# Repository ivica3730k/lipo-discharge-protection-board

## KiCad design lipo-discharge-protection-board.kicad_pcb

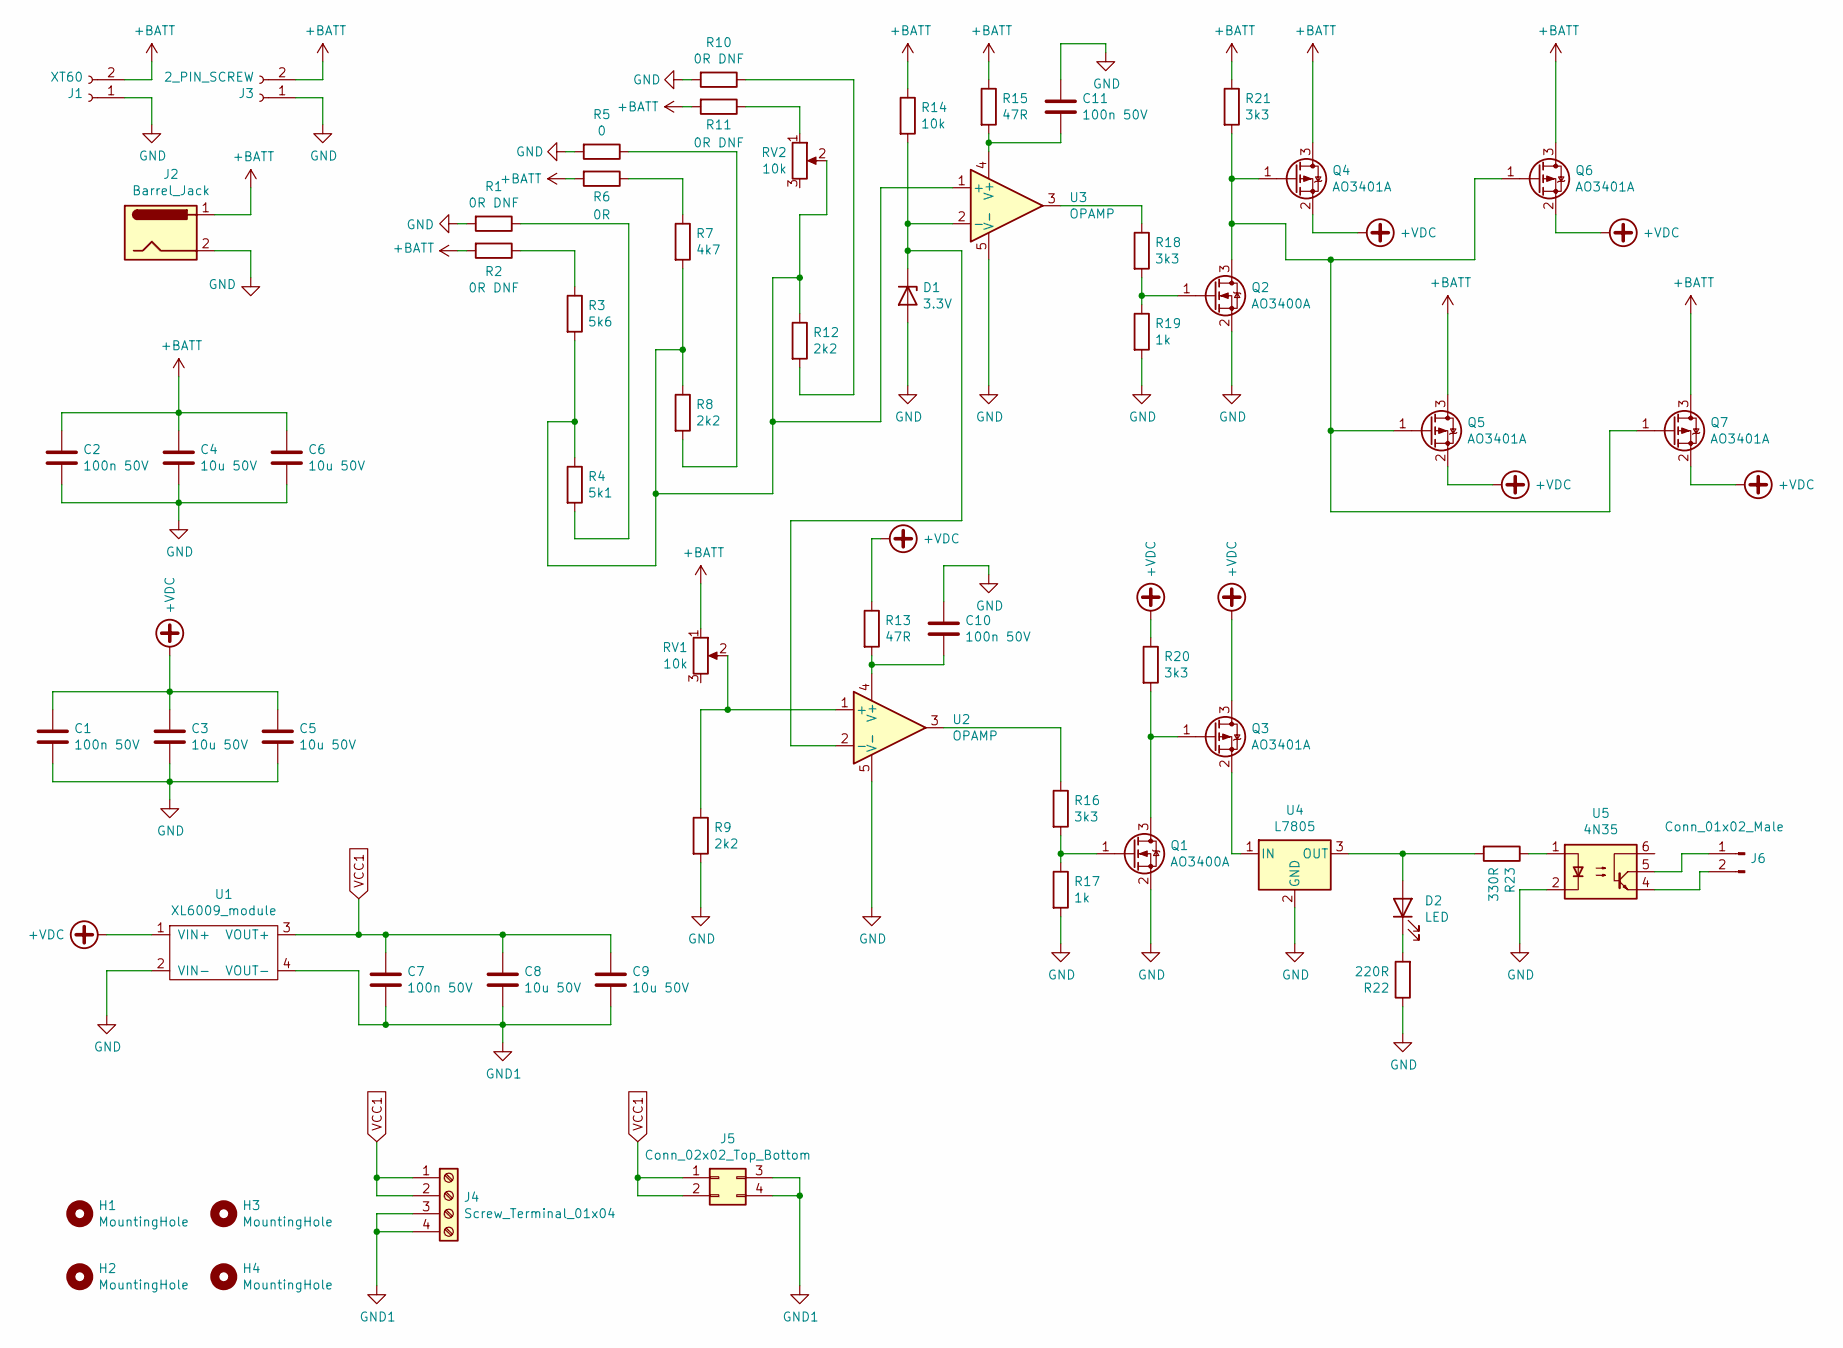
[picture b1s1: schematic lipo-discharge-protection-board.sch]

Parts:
C1, C2, C7, C10, C11: 100n 50V; C_0805_2012Metric_Pad1.18x1.45mm_HandSolder; LCSC C49678
C3, C4, C5, C6, C8, C9: 10u 50V; C_1206_3216Metric_Pad1.33x1.80mm_HandSolder; LCSC C13585
D1: 3.3V; D_MELF; LCSC C8056
D2: LED; LED_D5.0mm; LCSC C84256
H1, H2, H3, H4: MountingHole; MountingHole_3.2mm_M3
J1: XT60; AMASS_XT60-F_1x02_P7.20mm_Vertical
J2: Barrel_Jack; BarrelJack_Horizontal
J3: 2_PIN_SCREW; TerminalBlock_bornier-2_P5.08mm
J4: Screw_Terminal_01x04; TerminalBlock_bornier-4_P5.08mm
J5: Conn_02x02_Top_Bottom; Molex_Mini-Fit_Jr_5566-04A_2x02_P4.20mm_Vertical
J6: Conn_01x02_Male; PinHeader_1x02_P1.27mm_Vertical
Q1, Q2: AO3400A; SOT-23; LCSC C20917
Q3, Q4, Q5, Q6, Q7: AO3401A; SOT-23; LCSC AO3401A
R1, R2, R10, R11: 0R DNF; R_0805_2012Metric_Pad1.20x1.40mm_HandSolder
R3: 5k6; R_0805_2012Metric_Pad1.20x1.40mm_HandSolder; LCSC C4382
R4: 5k1; R_0805_2012Metric_Pad1.20x1.40mm_HandSolder; LCSC C27834
R5: 0; R_0805_2012Metric_Pad1.20x1.40mm_HandSolder
R6: 0R; R_0805_2012Metric_Pad1.20x1.40mm_HandSolder
R7: 4k7; R_0805_2012Metric_Pad1.20x1.40mm_HandSolder; LCSC C17673
R8, R9, R12: 2k2; R_0805_2012Metric_Pad1.20x1.40mm_HandSolder; LCSC C17520
R13, R15: 47R; R_0805_2012Metric_Pad1.20x1.40mm_HandSolder; LCSC C17714
R14: 10k; R_0805_2012Metric_Pad1.20x1.40mm_HandSolder; LCSC C17414
R16, R18, R20, R21: 3k3; R_0805_2012Metric_Pad1.20x1.40mm_HandSolder; LCSC C26010
R17, R19: 1k; R_0805_2012Metric_Pad1.20x1.40mm_HandSolder; LCSC C17513
R22: 220R; R_0805_2012Metric_Pad1.20x1.40mm_HandSolder; LCSC C17557
R23: 330R; R_0805_2012Metric_Pad1.20x1.40mm_HandSolder; LCSC C17630
RV1, RV2: 10k; Potentiometer_Bourns_3296W_Vertical
U1: XL6009_module; XL6009_module_SMT
U2, U3: OPAMP; SOIC-8_3.9x4.9mm_P1.27mm; LCSC C7433
U4: L7805; SOT-89-3_Handsoldering; LCSC C71136
U5: 4N35; DIP-6_W7.62mm

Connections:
+BATT: C2.1, C4.1, C6.1, J1.2, J2.1, J3.2, Q4.3 (D), Q5.3 (D), Q6.3 (D), Q7.3 (D), R2.2, R6.2, R11.2, R14.1, R15.1, R21.1, RV1.1
+VDC: C1.1, C3.1, C5.1, Q3.3 (D), Q4.2 (S), Q5.2 (S), Q6.2 (S), Q7.2 (S), R13.1, R20.1, U1.1 (VIN+)
GND: C1.2, C2.2, C3.2, C4.2, C5.2, C6.2, C10.1, C11.1, D1.2 (A), J1.1, J2.2, J3.1, Q1.2 (S), Q2.2 (S), R1.2, R5.2, R9.2, R10.2, R17.2, R19.2, R22.1, U1.2 (VIN-), U2.5 (V-), U3.5 (V-), U4.2 (GND), U5.2
GND1: C7.2, C8.2, C9.2, J4.3, J4.4, J5.3, J5.4, U1.4 (VOUT-)
unnamed: C10.2, R13.2, U2.4 (V+)
unnamed: C11.2, R15.2, U3.4 (V+)
unnamed: D1.1 (K), R14.2, U2.2 (-), U3.2 (-)
unnamed 7: D2.1 (K), R22.2; also elsewhere on the board
unnamed 8: D2.2 (A), R23.2, U4.3 (OUT); also elsewhere on the board
unnamed: J6.1, U5.5
unnamed: J6.2, U5.4
unnamed: Q1.1 (G), R16.2, R17.1
unnamed: Q1.3 (D), Q3.1 (G), R20.2
unnamed: Q2.1 (G), R18.2, R19.1
unnamed: Q2.3 (D), Q4.1 (G), Q5.1 (G), Q6.1 (G), Q7.1 (G), R21.2
unnamed: Q3.2 (S), U4.1 (IN)
unnamed: R1.1, R4.2
unnamed: R2.1, R3.1
unnamed: R5.1, R8.2
unnamed: R6.1, R7.1
unnamed: R9.1, RV1.2, U2.1 (+)
unnamed: R10.1, R12.2
unnamed: R11.1, RV2.1
unnamed: R3.2, R4.1, R7.2, R8.1, R12.1, RV2.2, U3.1 (+)
unnamed: R16.1, U2.3
unnamed: R18.1, U3.3
unnamed: R23.1, U5.1
VCC1: C7.1, C8.1, C9.1, J4.1, J4.2, J5.1, J5.2, U1.3 (VOUT+)

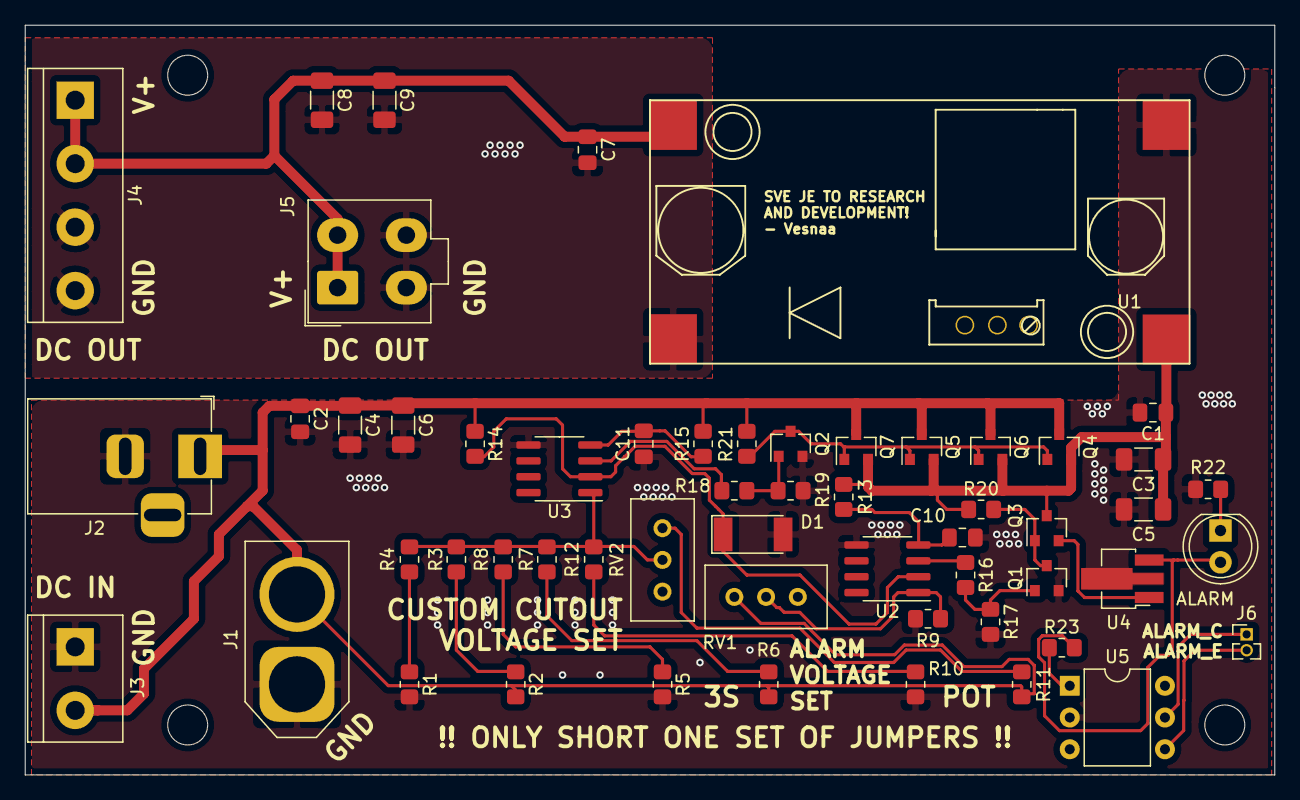
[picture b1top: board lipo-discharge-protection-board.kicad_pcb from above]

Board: 4 copper layers, 100.0 x 60.0 mm, 60 parts (0 on the bottom side), 28 nets.

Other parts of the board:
ALARM: LED; LED_D5.0mm

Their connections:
unnamed 7: ALARM.1; also elsewhere on the board
unnamed 8: ALARM.2; also elsewhere on the board

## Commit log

2021-09-29 Added project schematic
2021-10-01 Folder reorganising
2021-10-01 Added LCSC part numbers to components
2021-10-01 Reanotated schematic
2021-10-01 Assigned footprints to components
2021-10-01 Commit before shrinking to 1ch design
2021-10-02 Created pcb design
2021-10-02 Updated bad footprints and exported bom
2021-10-03 Added alarm circuit
2021-10-03 Added components for the alarm circuit and fixed wrong footprints
2021-10-04 Sync fix
2021-10-04 Added alarm circuit to PCB
2021-10-04 Updated PCB
2021-10-04 Added production files
2021-10-05 Added gitignore
2021-10-05 Added all project files and closing the project
2021-10-05 .gitignore is now working
2021-10-05 Added .gitignore and closing the project!
